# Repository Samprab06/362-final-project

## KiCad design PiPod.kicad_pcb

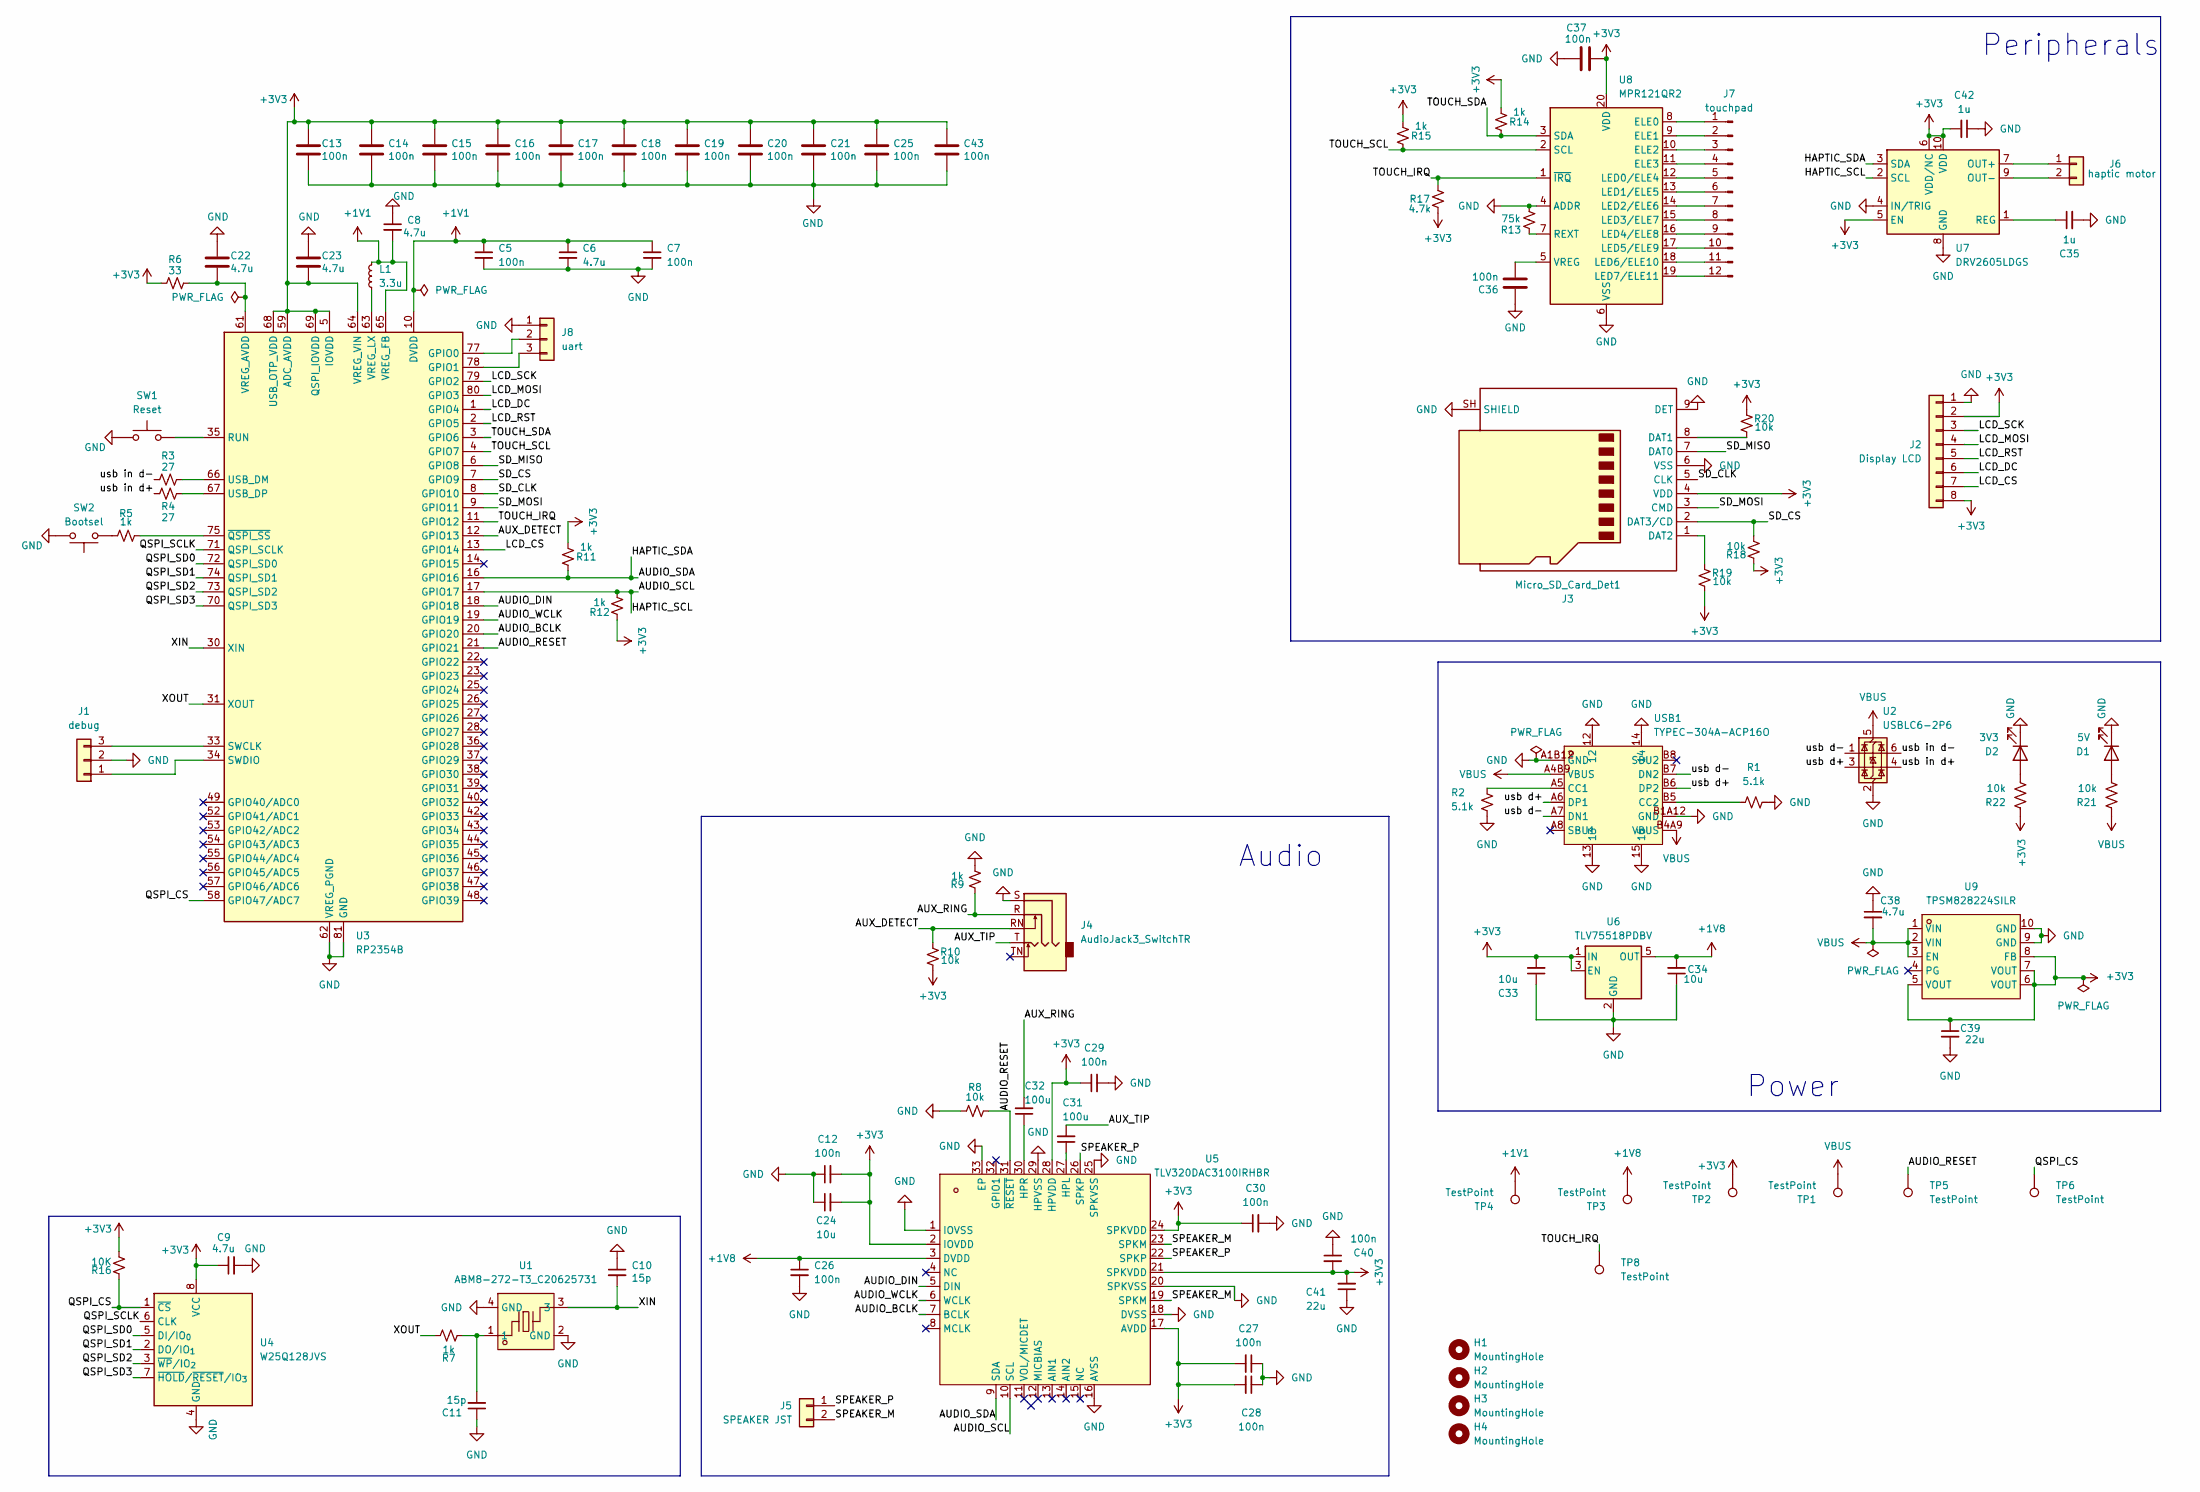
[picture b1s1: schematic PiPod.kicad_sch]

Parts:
C5, C7, C12, C13, C14, C15, C16, C17, C18, C19, C20, C21, C25, C26, C27, C28, C29, C30, C36, C37, C40, C43: 100n; C_0603_1608Metric
C6, C8, C9, C22, C23: 4.7u; C_0603_1608Metric
C10, C11: 15p; C_0603_1608Metric
C24, C33, C34: 10u; C_0603_1608Metric
C31, C32: 100u; C_1210_3225Metric
C35, C42: 1u; C_0603_1608Metric
C38: 4.7u; C_0805_2012Metric_Pad1.18x1.45mm_HandSolder
C39: 22u; C_0805_2012Metric_Pad1.18x1.45mm_HandSolder
C41: 22u; C_0805_2012Metric
D1: 5V; LED_0805_2012Metric_Pad1.15x1.40mm_HandSolder
D2: 3V3; LED_0805_2012Metric_Pad1.15x1.40mm_HandSolder
H1, H2, H3, H4: MountingHole; MountingHole_2.2mm_M2
J1: debug; PinHeader_1x03_P2.54mm_Vertical
J2: Display LCD; PinSocket_1x08_P2.00mm_Vertical
J3: Micro_SD_Card_Det1; microSD_HC_Molex_104031-0811
J4: AudioJack3_SwitchTR; Jack_3.5mm_CUI_SJ1-3515N_Horizontal
J5: SPEAKER JST; JST_PH_S2B-PH-K_1x02_P2.00mm_Horizontal
J6: haptic motor; PinHeader_1x02_P1.27mm_Vertical
J7: touchpad; PiPod_ClickWheel_MPR121_48mm
J8: uart; PinSocket_1x03_P2.54mm_Vertical
L1: 3.3u; IND-SMD_L2.0-W1.6_AOTA-B201610S3R3-101-T
R1, R2: 5.1k; R_0603_1608Metric
R3, R4: 27; R_0603_1608Metric
R5, R7, R9, R11, R12, R14, R15: 1k; R_0603_1608Metric
R6: 33; R_0603_1608Metric
R8, R10, R18, R19, R20: 10k; R_0603_1608Metric
R13: 75k; R_0603_1608Metric
R16: 10K; R_0603_1608Metric
R17: 4.7k; R_0805_2012Metric_Pad1.20x1.40mm_HandSolder
R21, R22: 10k; R_0805_2012Metric_Pad1.20x1.40mm_HandSolder
SW1: Reset; SW_PUSH_6mm
SW2: Bootsel; SW_PUSH_6mm
TP1, TP2, TP3, TP4, TP5, TP6, TP8: TestPoint; TestPoint_Pad_D1.0mm
U1: ABM8-272-T3_C20625731; CRYSTAL-SMD_4P-L3.2-W2.5-BL; MPN ABM8-272-T3; LCSC Part C20625731
U2: USBLC6-2P6; SOT-666
U3: RP2354B; QFN-80-1EP_10x10mm_P0.4mm_EP3.4x3.4mm
U4: W25Q128JVS; SOIC-8_5.3x5.3mm_P1.27mm
U5: TLV320DAC3100IRHBR; IC_ADS125H01IRHBT; MPN TLV320DAC3100IRHBR; LCSC Part C179677
U6: TLV75518PDBV; SOT-23-5
U7: DRV2605LDGS; TSSOP-10_3x3mm_P0.5mm
U8: MPR121QR2; UQFN-20_3x3mm_P0.4mm
U9: TPSM828224SILR; SIL0010D-MFG; MPN TPSM828224SILR; LCSC Part C2862913
USB1: TYPEC-304A-ACP16O; USB-SMD_TYPEC-304A-ACP16O; MPN TYPEC-304A-ACP16O; LCSC Part C2909610

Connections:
+1V1: C5.1, C6.1, C7.1, C8.2, L1.2, TP4.1 (1_1), U3.10 (DVDD), U3.32 (DVDD), U3.51 (DVDD), U3.65 (VREG_FB)
+1V8: C26.1, C34.2, TP3.1 (1_1), U5.3 (DVDD), U6.5 (OUT)
+3V3: C9.1, C12.2, C13.1, C14.1, C15.1, C16.1, C17.1, C18.1, C19.1, C20.1, C21.1, C23.2, C24.2, C25.1, C27.2, C28.2, C29.1, C30.1, C33.2, C37.1, C39.1, C40.2, C41.2, C42.2, C43.1, J2.2, J2.8, J3.4 (VDD), R6.1, R10.2, R11.1, R12.1, R14.1, R15.1, R16.2, R17.1, R18.1, R19.2, R20.1, R22.1, TP2.1 (1_1), U3.5 (IOVDD), U3.15 (IOVDD), U3.24 (IOVDD), U3.29 (IOVDD), U3.41 (IOVDD), U3.50 (IOVDD), U3.59 (ADC_AVDD), U3.60 (IOVDD), U3.64 (VREG_VIN), U3.68 (USB_OTP_VDD), U3.69 (QSPI_IOVDD), U3.76 (IOVDD), U4.8 (VCC), U5.2 (IOVDD), U5.17 (AVDD), U5.21 (SPKVDD), U5.24 (SPKVDD), U5.28 (HPVDD), U6.1 (IN), U6.3 (EN), U7.5 (EN), U7.6 (VDD/NC), U7.10 (VDD), U8.20 (VDD), U9.5 (VOUT), U9.6 (VOUT), U9.7 (VOUT), U9.8 (FB)
/AUDIO_BCLK: U3.20 (GPIO20), U5.7 (BCLK)
/AUDIO_DIN: U3.18 (GPIO18), U5.5 (DIN)
/AUDIO_RESET: R8.2, TP5.1 (1_1), U3.21 (GPIO21), U5.31 (~RESET)
/AUDIO_SCL: R12.2, U3.17 (GPIO17), U5.10 (SCL), U7.2 (SCL)
/AUDIO_SDA: R11.2, U3.16 (GPIO16), U5.9 (SDA), U7.3 (SDA)
/AUDIO_WCLK: U3.19 (GPIO19), U5.6 (WCLK)
/AUX_DETECT: J4.RN, R10.1, U3.12 (GPIO13)
/AUX_RING: C32.2, J4.R, R9.1
/AUX_TIP: C31.2, J4.T
/LCD_CS: J2.7, U3.13 (GPIO14)
/LCD_DC: J2.6, U3.1 (GPIO4)
/LCD_MOSI: J2.4, U3.80 (GPIO3)
/LCD_RST: J2.5, U3.2 (GPIO5)
/LCD_SCK: J2.3, U3.79 (GPIO2)
/QSPI_CS: R16.1, TP6.1 (1_1), U3.58 (GPIO47/ADC7), U4.1 (~CS)
/QSPI_SCLK: U3.71 (QSPI_SCLK), U4.6 (CLK)
/QSPI_SD0: U3.72 (QSPI_SD0), U4.5 (DI/IO_{0})
/QSPI_SD1: U3.74 (QSPI_SD1), U4.2 (DO/IO_{1})
/QSPI_SD2: U3.73 (QSPI_SD2), U4.3 (~WP/IO_{2})
/QSPI_SD3: U3.70 (QSPI_SD3), U4.7 (~HOLD/~RESET/IO_{3})
/SD_CLK: J3.5 (CLK), U3.8 (GPIO10)
/SD_CS: J3.2 (DAT3/CD), R18.2, U3.7 (GPIO9)
/SD_MISO: J3.7 (DAT0), U3.6 (GPIO8)
/SD_MOSI: J3.3 (CMD), U3.9 (GPIO11)
/SPEAKER_M: J5.2, U5.19 (SPKM), U5.23 (SPKM)
/SPEAKER_P: J5.1, U5.22 (SPKP), U5.26 (SPKP)
/TOUCH_IRQ: R17.2, TP8.1 (1_1), U3.11 (GPIO12), U8.1 (~IRQ)
/TOUCH_SCL: R15.2, U3.4 (GPIO7), U8.2 (SCL)
/TOUCH_SDA: R14.2, U3.3 (GPIO6), U8.3 (SDA)
/XIN: C10.2, U1.3, U3.30 (XIN)
/XOUT: R7.2, U3.31 (XOUT)
/usb d+: U2.3 (I/O2), USB1.A6 (DP1), USB1.B6 (DP2)
/usb d-: U2.1 (I/O1), USB1.A7 (DN1), USB1.B7 (DN2)
/usb in d+: R4.1, U2.4 (I/O2)
/usb in d-: R3.1, U2.6 (I/O1)
GND: C5.2, C6.2, C7.2, C8.1, C9.2, C10.1, C11.1, C12.1, C13.2, C14.2, C15.2, C16.2, C17.2, C18.2, C19.2, C20.2, C21.2, C22.1, C23.1, C24.1, C25.2, C26.2, C27.1, C28.1, C29.2, C30.2, C33.1, C34.1, C35.2, C36.1, C37.2, C38.1, C39.2, C40.1, C41.1, C42.1, C43.2, D1.1 (K), D2.1 (K), J1.2, J2.1, J3.6 (VSS), J3.9 (DET), J3.SH (SHIELD), J4.S, J8.1, R1.2, R2.2, R8.1, R9.2, R13.2, SW1.1, SW2.2, U1.2 (GND), U1.4 (GND), U2.2 (GND), U3.62 (VREG_PGND), U3.81 (GND), U4.4 (GND), U5.1 (IOVSS), U5.16 (AVSS), U5.18 (DVSS), U5.20 (SPKVSS), U5.25 (SPKVSS), U5.29 (HPVSS), U5.33 (EP), U6.2 (GND), U7.4 (IN/TRIG), U7.8 (GND), U8.4 (ADDR), U8.6 (VSS), U9.9 (GND), U9.10 (GND), USB1.12, USB1.13, USB1.14, USB1.15, USB1.A1B12 (GND), USB1.B1A12 (GND)
unnamed: C11.2, R7.1, U1.1
unnamed: D1.2 (A), R21.2
unnamed: D2.2 (A), R22.2
unnamed: J1.1, U3.34 (SWDIO)
unnamed: J1.3, U3.33 (SWCLK)
unnamed: J3.8 (DAT1), R20.2
unnamed: J3.1 (DAT2), R19.1
unnamed: J6.1, U7.7 (OUT+)
unnamed: J6.2, U7.9 (OUT-)
unnamed: J7.1, U8.8 (ELE0)
unnamed: J7.2, U8.9 (ELE1)
unnamed: J7.3, U8.10 (ELE2)
unnamed: J7.4, U8.11 (ELE3)
unnamed: J7.5, U8.12 (LED0/ELE4)
unnamed: J7.6, U8.13 (LED1/ELE5)
unnamed: J7.7, U8.14 (LED2/ELE6)
unnamed: J7.8, U8.15 (LED3/ELE7)
unnamed: J7.9, U8.16 (LED4/ELE8)
unnamed: J7.10, U8.17 (LED5/ELE9)
unnamed: J7.11, U8.18 (LED6/ELE10)
unnamed: J7.12, U8.19 (LED7/ELE11)
unnamed: J8.2, U3.77 (GPIO0)
unnamed: J8.3, U3.78 (GPIO1)
unnamed: R5.1, SW2.1
unnamed: SW1.2, U3.35 (RUN)
unnamed: R3.2, U3.66 (USB_DM)
unnamed: R4.2, U3.67 (USB_DP)
unnamed: C22.2, R6.2, U3.61 (VREG_AVDD)
unnamed: L1.1, U3.63 (VREG_LX)
unnamed: R5.2, U3.75 (~QSPI_SS)
unnamed: C31.1, U5.27 (HPL)
unnamed: C32.1, U5.30 (HPR)
unnamed: C35.1, U7.1 (REG)
unnamed: R13.1, U8.7 (REXT)
unnamed: C36.2, U8.5 (VREG)
unnamed: R2.1, USB1.A5 (CC1)
unnamed: R1.1, USB1.B5 (CC2)
VBUS: C38.2, R21.1, TP1.1 (1_1), U2.5 (VBUS), U9.1 (VIN), U9.2 (VIN), U9.3 (EN), USB1.A4B9 (VBUS), USB1.B4A9 (VBUS)

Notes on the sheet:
Power
Audio
Peripherals

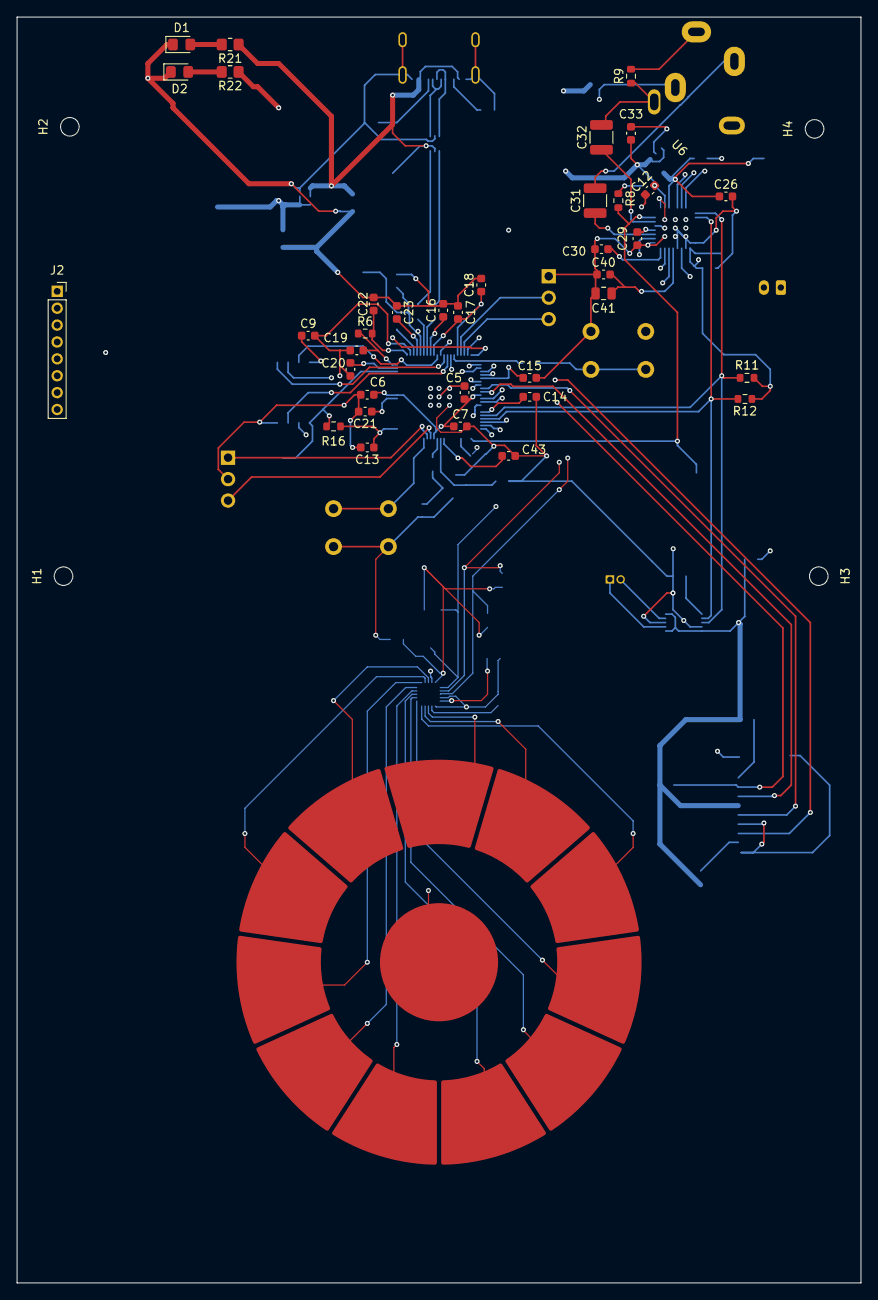
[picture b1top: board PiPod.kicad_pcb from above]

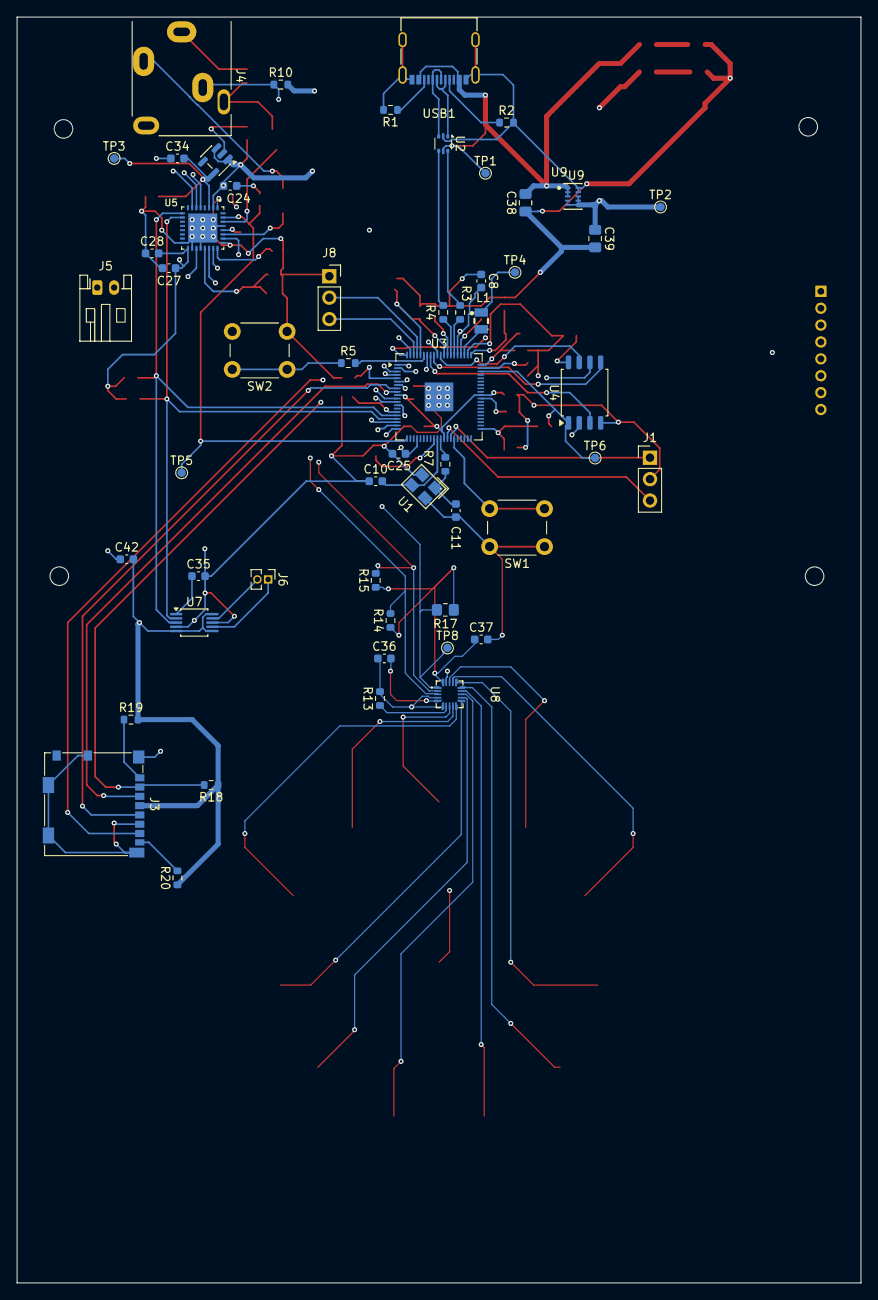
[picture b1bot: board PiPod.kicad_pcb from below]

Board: 4 copper layers, 100.0 x 150.0 mm, 95 parts (54 on the bottom side), 77 nets.
